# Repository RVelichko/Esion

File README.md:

## Серис обслуживания устройств
[Описание команд взимодействия с сервисом](./docs/web_service_commands.md)

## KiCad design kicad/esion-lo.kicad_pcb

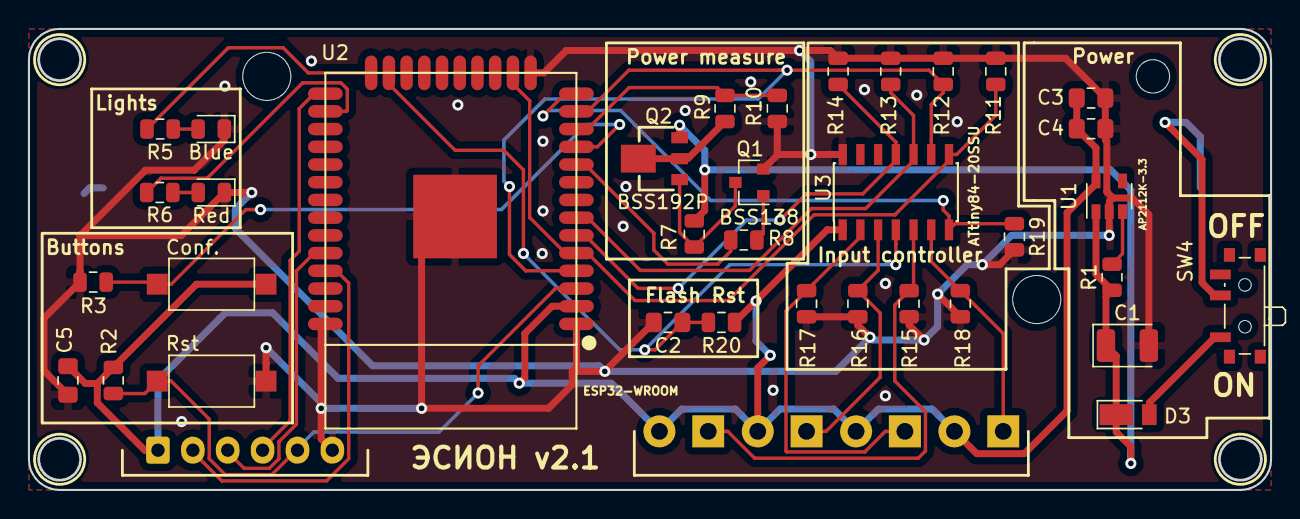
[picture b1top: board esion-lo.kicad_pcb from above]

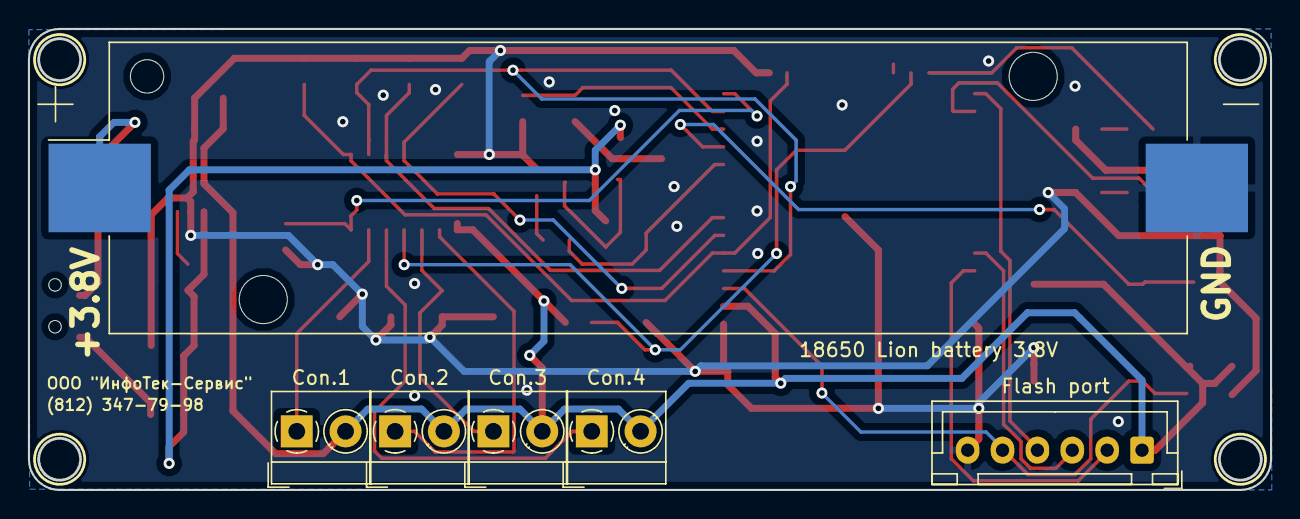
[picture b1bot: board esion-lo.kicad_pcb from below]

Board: 2 copper layers, 89.0 x 33.0 mm, 41 parts (6 on the bottom side), 30 nets.

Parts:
18650 Lion battery 3.8V: Battery_Cell; BatteryHolder_Keystone_1042_1x18650
Blue: Blue; LED_0805_2012Metric
C1: 10uF/10V; CP_EIA-3528-21_Kemet-B
C2, C3, C5: 0.1uF; C_0805_2012Metric_Pad1.15x1.40mm_HandSolder
C4: 10uF; C_0805_2012Metric_Pad1.15x1.40mm_HandSolder
Con.1: Connector 1; TerminalBlock_MetzConnect_Type059_RT06302HBWC_1x02_P3.50mm_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
Con.2: Connector 2; TerminalBlock_MetzConnect_Type059_RT06302HBWC_1x02_P3.50mm_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
Con.3: Connector 3; TerminalBlock_MetzConnect_Type059_RT06302HBWC_1x02_P3.50mm_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
Con.4: Connector 4; TerminalBlock_MetzConnect_Type059_RT06302HBWC_1x02_P3.50mm_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
Conf.: SW2; SW_SPST_CK_RS282G05A3
D3: MBR120; D_PowerDI-123
Flash port: ESP Flash; JST_XH_B06B-XH-A_1x06_P2.50mm_Vertical
Q1: BSS138; SOT-23
Q2: BSS192P; SOT89R_INFINEON
R1, R2, R3, R11, R12, R13, R14, R15, R16, R17, R18, R19: 10K; R_0805_2012Metric
R5, R6, R20: 220; R_0805_2012Metric
R7, R10: 20K; R_0805_2012Metric
R8: 100; R_0805_2012Metric
R9: 4.7K; R_0805_2012Metric
Red: Red; LED_0805_2012Metric
Rst: SW1; SW_SPST_CK_RS282G05A3
SW4: POWER; SW_SPDT_PCM12
U1: AP2112K-3.3; SOT-23-5
U2: ESP32-WROOM
U3: ATtiny84-20SSU; SOIC-14_3.9x8.7mm_P1.27mm

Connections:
+3V3: C3.2, C4.1, C5.1, Con.1.2, Con.2.2, Con.3.2, Con.4.2, Conf..1, Flash port.1, R2.1, R20.1, U1.5, U2.2, U3.1
+3V8: 18650 Lion battery 3.8V.1, SW4.2
GNDREF: 18650 Lion battery 3.8V.2, Blue.1, C1.2, C2.2, C3.1, C4.2, C5.2, Flash port.6, Q1.2, R3.1, R10.2, R11.2, R12.2, R13.2, R14.2, R15.2, R16.2, R17.2, R18.2, R19.2, Red.1, Rst.1, U1.2, U2.1, U2.15, U2.38, U2.39, U3.14
IO25: R8.1, U2.10
IO27: R9.2, R10.1, U2.12
M1: C1.1, D3.1, Q2.3, R1.1, R7.1, U1.1
unnamed: C2.1, R20.2, U2.23, U3.4
unnamed: Blue.2, R5.1
unnamed: R6.2, Red.2
unnamed: D3.2, SW4.1
unnamed: Flash port.2, U2.35
unnamed: Flash port.3, U2.34
unnamed: Flash port.4, U2.25
unnamed: Flash port.5, R2.2, Rst.2, U2.3
unnamed: Con.1.1, R18.1, U3.6
unnamed: Con.2.1, R17.1, U3.2
unnamed: Con.3.1, R16.1, U3.3
unnamed: Con.4.1, R15.1, U3.5
unnamed: Q1.1, R8.2
unnamed: Q1.3, Q2.1, R7.2
unnamed: Q2.2, R9.1
unnamed: R1.2, U1.3
unnamed: Conf..2, R3.2, U2.11
unnamed: R5.2, U2.24
unnamed: R6.1, U2.26
unnamed: R11.1, U2.5, U2.16, U3.8
unnamed: R12.1, U2.4, U2.13, U3.9
unnamed: R13.1, U2.7, U3.10
unnamed: R14.1, U2.6, U3.11
unnamed: R19.1, U2.14, U3.7

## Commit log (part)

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2018-11-19 Start.
2018-11-19 First
2018-11-23 Добавлена схема контроллера.
2018-11-23 Отлажена отправка данных на сервер.
2018-11-25 ЗАвершена первая версия контроллера.
2018-11-25 Убраны избыточные файлы.
2019-02-11 Добавлена обработка кнопки перехода в режим конфигурирования.
2019-03-22 Исправлено падение прошивки при подключение к не существующему серверу.
2019-03-22 Исправлена логика отправки счётчиков на сервер.
2019-03-22 Добавлен класс шифрования данных.
2019-04-04 Рабочая версия 1.1
2019-04-09 Наведение порядка.
2019-04-11 Добавлен фассад базы данных.
2019-04-16 Изменена версия сервера на работу с БД.
2019-04-16 Доработано логирование, исправлен скрипт сборки.
2019-04-16 Отлажена доставка информации об устройствах из базы на страницу оператора.
2019-04-17 Добавлены функции детального отображения информации о контроллерах.
2019-04-18 Добавлена функция дополнительного запроса устройств.
2019-04-27 Версия 2.х.
2019-05-18 Добавлен запуск прерывания по таймеру для отсечки зависаний.
2019-05-23 Добавлены модели корпусов, оптимизированных под горячую гибку.
2019-05-30 Исправлены позиции отверстий в корпусах.
2019-06-29 Добавлен сервер поискового индекса.
2019-06-29 Добавлена отладочная страница сервера поискового индекса.
2019-06-29 Отлажена работа поискового индекса.
2019-07-07 Добавлен генератор отчёта, добавлены обработчики команд.
2019-07-09 Отлажена обработка команд сервера. Добавлен генератор тестовых данных.
2019-07-18 Добавлено отчиска старых токенов. Добавлена сортировка запрашиваемых списков.
2019-07-22 Добавлена команда на возврат количества устройств в критическом состоянии.
2019-07-22 Исправлена работа генератора репортов.
2019-07-23 Добавлено удаление устаревших репортов.
2019-07-24 Доработан формат выпуска отчёта.
2019-07-26 Добавлен выбор по пользовательской коллекции, Добавлено исключение массива счётчиков в ответе.
2019-07-27 Добавлена отправка прогресса формирования репорта.
2019-07-29 Добавлена документация с описанием команд сервиса.
2019-07-29 Исправлена документация.
2019-07-29 Добавлен поиск по времени.
2019-07-29 Добавлен возврат количества критических событий для одного устройства. Исправлен формат отчёта.
2019-07-30 Исправлено получение списков по дате.
2019-07-30 Добавлен поиск устройст по диапазону дат.
2019-07-30 Исправлена генерация репортов.
2019-08-01 Исправлена фильтрация по дате для событий.
2019-08-02 Расширен функционал по запросу данных из базы.
2019-08-09 Добавлен вывод значений предыдущих потреблений в отчёт.
2019-08-15 Добавлен скрипт автопрограмматора.
2019-08-15 Аерсия автопрограмматора без тестов.
2019-08-16 Добавлены пояснения для ssh.
2019-09-04 Подготовлена продуктовая версия вёрстки настроек устройства.
2019-09-17 Добавлена стартовая версия страницы управления администраторами сервиса устройств.
2019-10-07 Исправлен сервис и таймер перезапуска.
2019-10-08 Добавлены файлы верстки.
2019-11-14 Доработана страница конфигурирования.
2019-11-14 Добавлены исходники страницы настроек устройства.
2020-03-03 Добавлены и исправлены описания.
2020-06-07 Bump websocket-extensions from 0.1.3 to 0.1.4 in /UsersAdminPage
    Bumps [websocket-extensions](https://github.com/faye/websocket-extensions-node) from 0.1.3 to 0.1.4.
    - [Release notes](https://github.com/faye/websocket-extensions-node/releases)
    - [Changelog](https://github.com/faye/websocket-extensions-node/blob/master/CHANGELOG.md)
    - [Commits](https://github.com/faye/websocket-extensions-node/compare/0.1.3...0.1.4)
2020-07-18 Bump lodash from 4.17.15 to 4.17.19 in /UsersAdminPage
    Bumps [lodash](https://github.com/lodash/lodash) from 4.17.15 to 4.17.19.
    - [Release notes](https://github.com/lodash/lodash/releases)
    - [Commits](https://github.com/lodash/lodash/compare/4.17.15...4.17.19)
2020-07-18 Bump lodash from 4.17.15 to 4.17.19 in /esion-conf-page
    Bumps [lodash](https://github.com/lodash/lodash) from 4.17.15 to 4.17.19.
    - [Release notes](https://github.com/lodash/lodash/releases)
    - [Commits](https://github.com/lodash/lodash/compare/4.17.15...4.17.19)
2020-07-31 Bump elliptic from 6.5.1 to 6.5.3 in /UsersAdminPage
    Bumps [elliptic](https://github.com/indutny/elliptic) from 6.5.1 to 6.5.3.
    - [Release notes](https://github.com/indutny/elliptic/releases)
    - [Commits](https://github.com/indutny/elliptic/compare/v6.5.1...v6.5.3)
2020-08-01 Bump elliptic from 6.5.0 to 6.5.3 in /esion-conf-page
    Bumps [elliptic](https://github.com/indutny/elliptic) from 6.5.0 to 6.5.3.
    - [Release notes](https://github.com/indutny/elliptic/releases)
    - [Commits](https://github.com/indutny/elliptic/compare/v6.5.0...v6.5.3)
2020-09-04 Bump node-sass from 4.12.0 to 4.13.1 in /UsersAdminPage
    Bumps [node-sass](https://github.com/sass/node-sass) from 4.12.0 to 4.13.1.
    - [Release notes](https://github.com/sass/node-sass/releases)
    - [Changelog](https://github.com/sass/node-sass/blob/master/CHANGELOG.md)
    - [Commits](https://github.com/sass/node-sass/compare/v4.12.0...v4.13.1)
2020-09-04 Bump node-sass from 4.12.0 to 4.13.1 in /esion-conf-page
    Bumps [node-sass](https://github.com/sass/node-sass) from 4.12.0 to 4.13.1.
    - [Release notes](https://github.com/sass/node-sass/releases)
    - [Changelog](https://github.com/sass/node-sass/blob/master/CHANGELOG.md)
    - [Commits](https://github.com/sass/node-sass/compare/v4.12.0...v4.13.1)
2020-09-10 Bump http-proxy from 1.17.0 to 1.18.1 in /esion-conf-page
    Bumps [http-proxy](https://github.com/http-party/node-http-proxy) from 1.17.0 to 1.18.1.
    - [Release notes](https://github.com/http-party/node-http-proxy/releases)
    - [Changelog](https://github.com/http-party/node-http-proxy/blob/master/CHANGELOG.md)
    - [Commits](https://github.com/http-party/node-http-proxy/compare/1.17.0...1.18.1)
2020-11-25 Bump highlight.js from 9.15.10 to 9.18.5 in /UsersAdminPage
    Bumps [highlight.js](https://github.com/highlightjs/highlight.js) from 9.15.10 to 9.18.5.
    - [Release notes](https://github.com/highlightjs/highlight.js/releases)
    - [Changelog](https://github.com/highlightjs/highlight.js/blob/9.18.5/CHANGES.md)
    - [Commits](https://github.com/highlightjs/highlight.js/compare/9.15.10...9.18.5)
2020-11-25 Bump highlight.js from 9.15.10 to 9.18.5 in /esion-conf-page
    Bumps [highlight.js](https://github.com/highlightjs/highlight.js) from 9.15.10 to 9.18.5.
    - [Release notes](https://github.com/highlightjs/highlight.js/releases)
    - [Changelog](https://github.com/highlightjs/highlight.js/blob/9.18.5/CHANGES.md)
    - [Commits](https://github.com/highlightjs/highlight.js/compare/9.15.10...9.18.5)
2021-01-05 Bump axios from 0.19.0 to 0.21.1 in /UsersAdminPage
    Bumps [axios](https://github.com/axios/axios) from 0.19.0 to 0.21.1.
    - [Release notes](https://github.com/axios/axios/releases)
    - [Changelog](https://github.com/axios/axios/blob/v0.21.1/CHANGELOG.md)
    - [Commits](https://github.com/axios/axios/compare/v0.19.0...v0.21.1)
2021-01-05 Bump axios from 0.19.0 to 0.21.1 in /esion-conf-page
    Bumps [axios](https://github.com/axios/axios) from 0.19.0 to 0.21.1.
    - [Release notes](https://github.com/axios/axios/releases)
    - [Changelog](https://github.com/axios/axios/blob/v0.21.1/CHANGELOG.md)
    - [Commits](https://github.com/axios/axios/compare/v0.19.0...v0.21.1)
2021-03-09 Bump elliptic from 6.5.1 to 6.5.4 in /UsersAdminPage
    Bumps [elliptic](https://github.com/indutny/elliptic) from 6.5.1 to 6.5.4.
    - [Release notes](https://github.com/indutny/elliptic/releases)
    - [Commits](https://github.com/indutny/elliptic/compare/v6.5.1...v6.5.4)
2021-03-31 Bump y18n from 3.2.1 to 3.2.2 in /UsersAdminPage
    Bumps [y18n](https://github.com/yargs/y18n) from 3.2.1 to 3.2.2.
    - [Release notes](https://github.com/yargs/y18n/releases)
    - [Changelog](https://github.com/yargs/y18n/blob/master/CHANGELOG.md)
    - [Commits](https://github.com/yargs/y18n/commits)
2021-03-31 Bump y18n from 3.2.1 to 3.2.2 in /esion-conf-page
    Bumps [y18n](https://github.com/yargs/y18n) from 3.2.1 to 3.2.2.
    - [Release notes](https://github.com/yargs/y18n/releases)
    - [Changelog](https://github.com/yargs/y18n/blob/master/CHANGELOG.md)
    - [Commits](https://github.com/yargs/y18n/commits)
2021-05-08 Bump url-parse from 1.4.7 to 1.5.1 in /UsersAdminPage
    Bumps [url-parse](https://github.com/unshiftio/url-parse) from 1.4.7 to 1.5.1.
    - [Release notes](https://github.com/unshiftio/url-parse/releases)
    - [Commits](https://github.com/unshiftio/url-parse/compare/1.4.7...1.5.1)
2021-05-08 Bump url-parse from 1.4.7 to 1.5.1 in /esion-conf-page
    Bumps [url-parse](https://github.com/unshiftio/url-parse) from 1.4.7 to 1.5.1.
    - [Release notes](https://github.com/unshiftio/url-parse/releases)
    - [Commits](https://github.com/unshiftio/url-parse/compare/1.4.7...1.5.1)
2021-05-10 Bump lodash from 4.17.15 to 4.17.21 in /UsersAdminPage
    Bumps [lodash](https://github.com/lodash/lodash) from 4.17.15 to 4.17.21.
    - [Release notes](https://github.com/lodash/lodash/releases)
    - [Commits](https://github.com/lodash/lodash/compare/4.17.15...4.17.21)
2021-05-10 Bump lodash from 4.17.15 to 4.17.21 in /esion-conf-page
    Bumps [lodash](https://github.com/lodash/lodash) from 4.17.15 to 4.17.21.
    - [Release notes](https://github.com/lodash/lodash/releases)
    - [Commits](https://github.com/lodash/lodash/compare/4.17.15...4.17.21)
2021-05-11 Bump hosted-git-info from 2.8.4 to 2.8.9 in /esion-conf-page
    Bumps [hosted-git-info](https://github.com/npm/hosted-git-info) from 2.8.4 to 2.8.9.
    - [Release notes](https://github.com/npm/hosted-git-info/releases)
    - [Changelog](https://github.com/npm/hosted-git-info/blob/v2.8.9/CHANGELOG.md)
    - [Commits](https://github.com/npm/hosted-git-info/compare/v2.8.4...v2.8.9)
2021-05-25 Bump browserslist from 4.7.0 to 4.16.6 in /UsersAdminPage
    Bumps [browserslist](https://github.com/browserslist/browserslist) from 4.7.0 to 4.16.6.
    - [Release notes](https://github.com/browserslist/browserslist/releases)
    - [Changelog](https://github.com/browserslist/browserslist/blob/main/CHANGELOG.md)
    - [Commits](https://github.com/browserslist/browserslist/compare/4.7.0...4.16.6)
2021-05-25 Bump browserslist from 4.6.6 to 4.16.6 in /esion-conf-page
    Bumps [browserslist](https://github.com/browserslist/browserslist) from 4.6.6 to 4.16.6.
    - [Release notes](https://github.com/browserslist/browserslist/releases)
    - [Changelog](https://github.com/browserslist/browserslist/blob/main/CHANGELOG.md)
    - [Commits](https://github.com/browserslist/browserslist/compare/4.6.6...4.16.6)
2021-05-28 Bump dns-packet from 1.3.1 to 1.3.4 in /UsersAdminPage
    Bumps [dns-packet](https://github.com/mafintosh/dns-packet) from 1.3.1 to 1.3.4.
    - [Release notes](https://github.com/mafintosh/dns-packet/releases)
    - [Changelog](https://github.com/mafintosh/dns-packet/blob/master/CHANGELOG.md)
    - [Commits](https://github.com/mafintosh/dns-packet/compare/v1.3.1...v1.3.4)
2021-05-28 Bump dns-packet from 1.3.1 to 1.3.4 in /esion-conf-page
    Bumps [dns-packet](https://github.com/mafintosh/dns-packet) from 1.3.1 to 1.3.4.
    - [Release notes](https://github.com/mafintosh/dns-packet/releases)
    - [Changelog](https://github.com/mafintosh/dns-packet/blob/master/CHANGELOG.md)
    - [Commits](https://github.com/mafintosh/dns-packet/compare/v1.3.1...v1.3.4)
